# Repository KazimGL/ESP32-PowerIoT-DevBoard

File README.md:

# ESP32 PowerIoT Dev Board

**A battery-powered ESP32 development board with onboard Li-ion charging, protection, regulation, and sensor support — designed end-to-end in KiCad.**

Designed by **Kazim Bhojani** ([KaizBuilts](#)) — a fresher PCB design project built to learn the complete hardware design workflow from schematic to fabrication-ready Gerbers.

---

## 📋 Overview

This board combines four functional subsystems into a single 2-layer PCB:

| Block | Function |
|---|---|
| **Power** | USB-C input, ESD protection, TP4056 Li-ion charging, DW01A + FS8205A battery protection, AP2112K-3.3 regulation, battery voltage sensing |
| **Processor** | ESP32-WROOM-32E module with reset/boot circuitry |
| **Communication** | CH340C USB-UART bridge with auto-program (DTR/RTS reset) circuit, I2C breakout |
| **I/O** | Dual GPIO breakout headers (1×15 each), user LED, user button, BME280 environmental sensor |

---

## ⚙️ Specs

- **MCU:** ESP32-WROOM-32E (WiFi + Bluetooth)
- **Charging:** TP4056, USB-C input, configurable charge current
- **Protection:** DW01A + FS8205A (overcharge / overdischarge / short-circuit)
- **Regulation:** AP2112K-3.3, 600mA LDO
- **Sensor:** BME280 (temperature, humidity, pressure) over I2C
- **Layers:** 2-layer PCB
- **Design tool:** KiCad 10.0.5
- **Board size:** ~65mm × 50mm

---

## 🖼️ Images

**PCB Layout / Routing**

**3D Render**

**Schematic**
📄 [schematic.pdf](schematic.pdf)

**3D Design Overview**
📄 [PRoject_cv.pdf](PRoject_cv.pdf)

---

## 🧠 Design Process & AI-Assisted Workflow

This project was built while learning PCB design fundamentals from scratch, using **Claude (Anthropic)** as a design-review assistant throughout the process — not to generate the design automatically, but to:

- Review each schematic block (Power, Processor, Communication, I/O) for wiring correctness before moving forward
- Explain *why* certain circuits work the way they do (e.g., the EN/IO0 auto-reset logic, battery protection MOSFET gate drive, I2C pull-up sizing)
- Walk through ERC/DRC error messages line-by-line and explain root causes rather than just handing over a fix
- Catch real mistakes along the way (several were my own, and at least one was the AI's — an incorrect DTR/RTS pin mapping that was caught and corrected by cross-checking against esptool's actual reset sequence rather than assumption)

This was an intentionally iterative process: wire a section → verify in ERC → get it reviewed → fix → repeat. Every connection in this board was manually drawn, checked, and understood — the AI's role was review and explanation, not auto-generation.

---

## 🐛 Real Issues Faced During This Build

Documenting these because they were the most time-consuming (and most educational) parts of the project:

1. **KiCad global symbol library table accidentally broken** — while trying to fix a missing footprint library path, the entire global symbol library table collapsed down to a single broken entry, causing 72 cascading ERC warnings across unrelated components (`power`, `Diode`, `Switch`, `Connector` libraries all failed to load). Fixed using KiCad's **"Reset Libraries"** button in the Symbol Libraries manager.

2. **Custom part (FS8205A) had no native KiCad footprint** — imported via `easyeda2kicad` from its LCSC part number, which required linking both a symbol library *and* a separate footprint library (`.pretty` folder) through two different dialogs in two different KiCad editors (Schematic Editor vs. PCB Editor) — not obvious at first.

3. **Duplicate global labels merging unrelated nets** — reused generic labels like `INPUT` and `OUTPUT` in multiple places on the schematic, which KiCad silently merged into a single net across the whole sheet, causing misleading ERC warnings until traced back and renamed to unique, meaningful net names (`VBUS_FUSED`, `3V3`, `-BATT`, etc).

4. **USB-C footprint/symbol pin-count mismatch** — J1 was assigned a 6-pin "power only" USB-C footprint while the schematic symbol used the full 16-pin USB 2.0 pinout (including D+/D−), causing 10 pad-not-found errors during PCB sync. Fixed by selecting the correct 16-pin footprint (`USB_C_Receptacle_HRO_TYPE-C-31-M-12`) matching the real connector's datasheet.

5. **Invalid reference designators blocking PCB sync** — two LED symbols were accidentally named `Green(Done)1` and `RED(charging)1` instead of standard alphanumeric designators, which KiCad's schematic/ERC tolerated but the PCB sync step rejected outright. Renamed to proper `D4`/`D5` format.

6. **DRC hole-size violation on the ESP32 module footprint** — the ESP32-WROOM-32E footprint's castellated pads required a 0.2mm minimum drill size, but the board's design rules were set to a 0.3mm minimum, causing 21 repeated violations. Resolved by adjusting the board's minimum drill size constraint to match both the footprint and the target fab's actual capability.

7. **Incomplete thermal relief connections** on copper pour zones for small shield/ground pads — fixed by reducing the thermal relief gap and spoke width settings to better fit smaller pad geometries.

Each of these was worked through methodically: understand the error → identify root cause → fix → re-verify, rather than blindly applying fixes.

---

## 📁 Repository Contents

```
project_CV.kicad_pro    → KiCad project file
project_CV.kicad_sch    → Schematic source
project_CV.kicad_pcb    → PCB layout source
schematic.pdf           → Exported schematic (all 4 blocks)
PRoject_cv.pdf          → Full project document
*.png                   → PCB layout / 3D render screenshots
README.md               → This file
```

---

## 🔧 Tools Used

- **KiCad 10.0.5** — schematic capture, PCB layout, DRC/ERC
- **easyeda2kicad** — custom part import (FS8205A battery protection MOSFET)
- **Claude (Anthropic)** — design review and debugging assistant

---

---

*Built as a learning project to understand the full PCB design lifecycle — schematic capture, component selection, DFM, fabrication file generation, and bring-up — end to end.*

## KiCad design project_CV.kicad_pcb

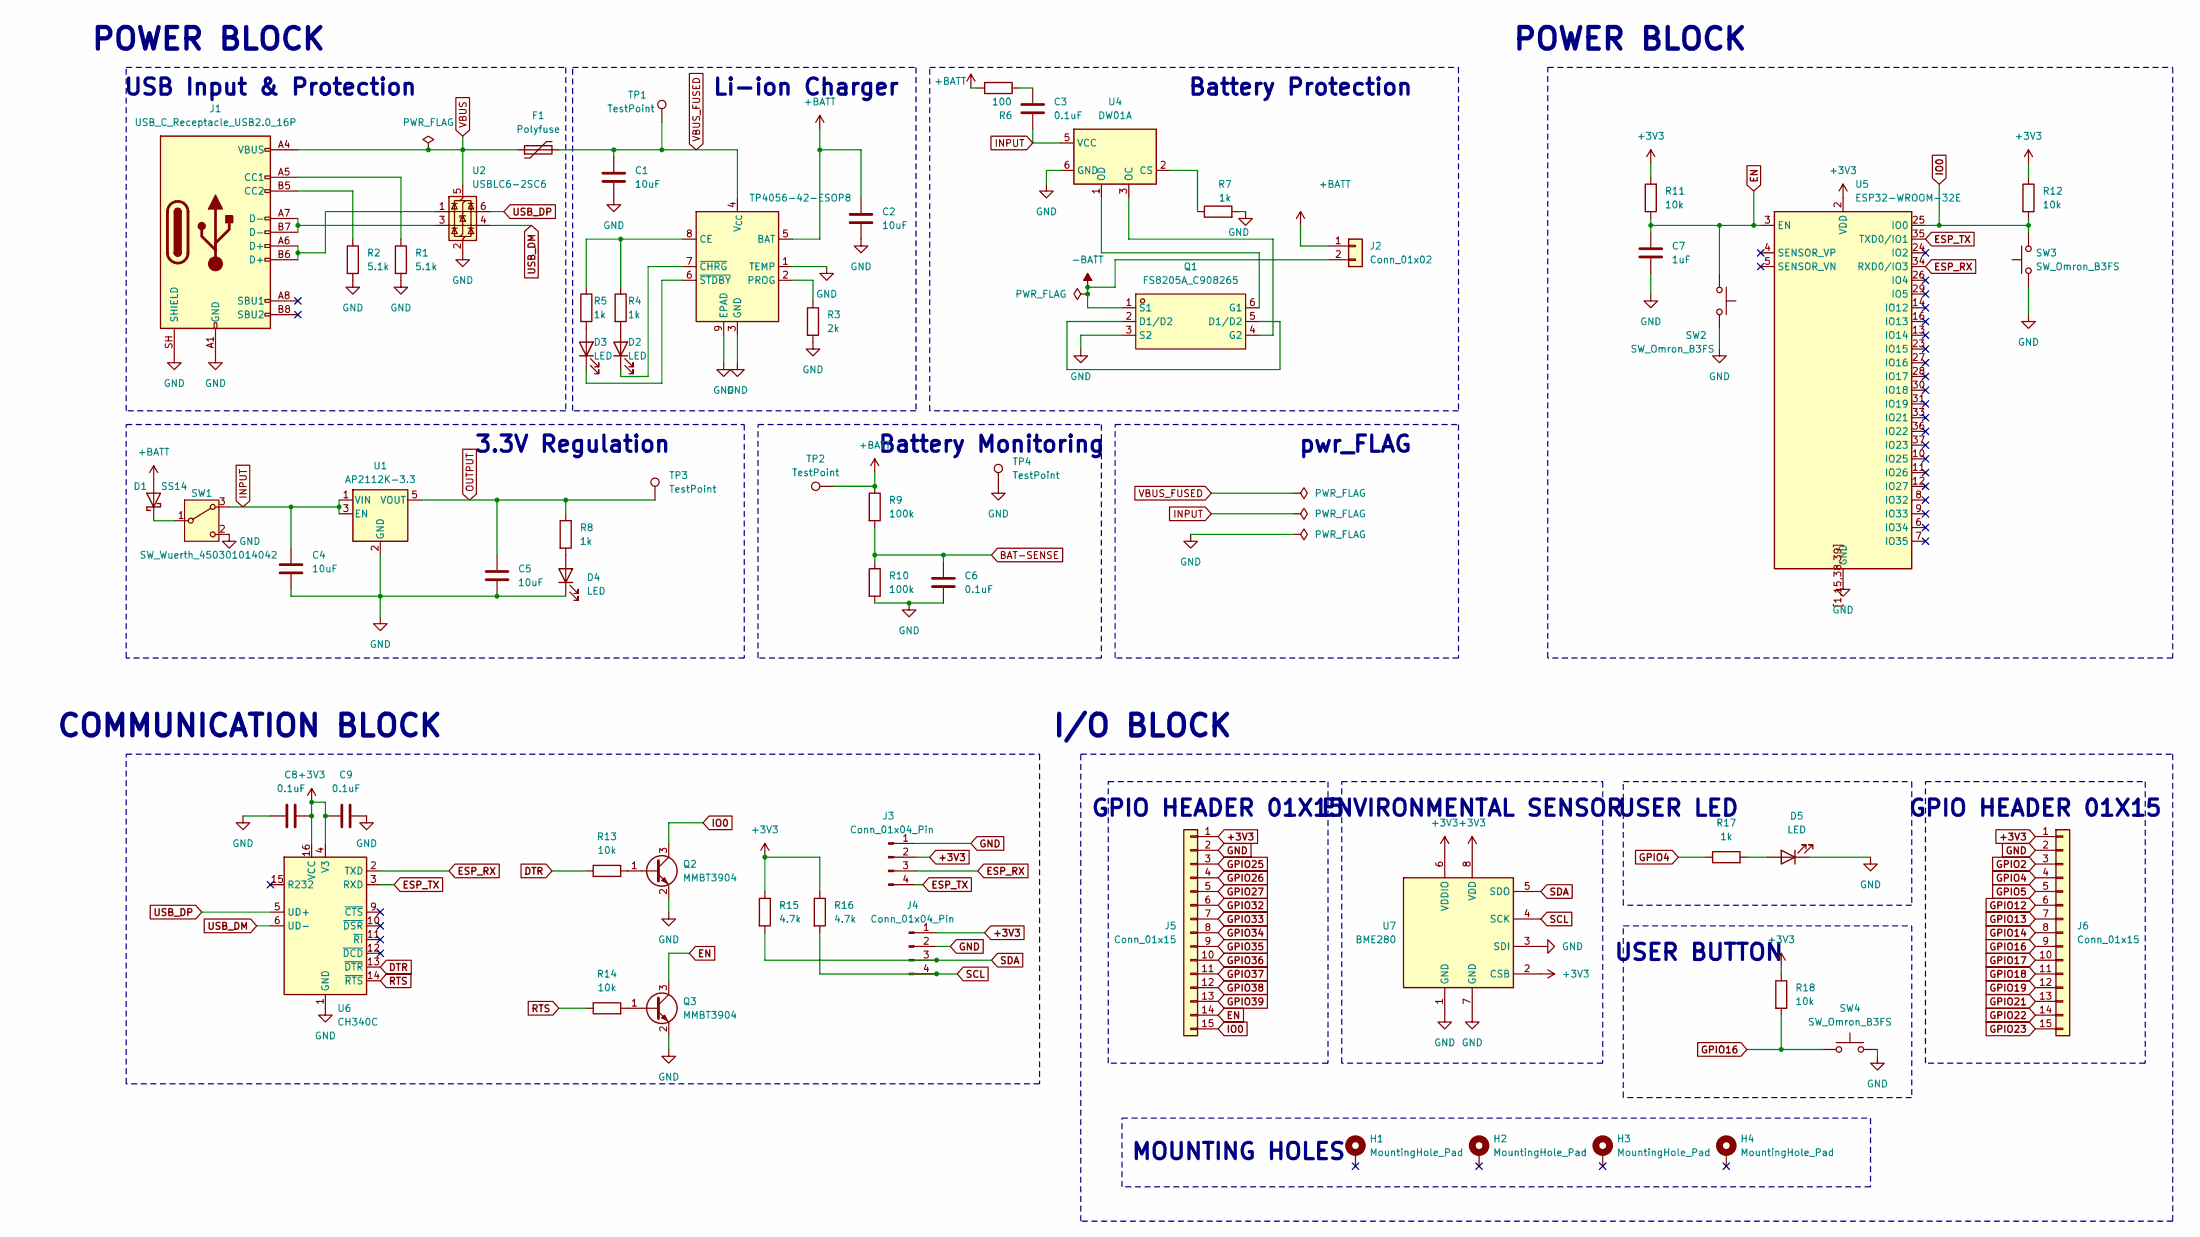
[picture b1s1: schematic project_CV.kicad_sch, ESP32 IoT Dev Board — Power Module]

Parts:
C1, C2, C4, C5: 10uF; C_0805_2012Metric
C3, C6, C8, C9: 0.1uF; C_0603_1608Metric
C7: 1uF; C_0603_1608Metric
D1: SS14; D_SMA
D2, D3, D4, D5: LED; LED_0805_2012Metric
F1: Polyfuse; Fuse_1206_3216Metric
H1, H2, H3, H4: MountingHole_Pad; MountingHole_2.2mm_M2_Pad
J1: USB_C_Receptacle_USB2.0_16P; USB_C_Receptacle_HRO_TYPE-C-31-M-12
J2: Conn_01x02; JST_PH_B2B-PH-K_1x02_P2.00mm_Vertical
J3, J4: Conn_01x04_Pin; PinHeader_1x04_P2.54mm_Vertical
J5, J6: Conn_01x15; PinHeader_1x15_P2.54mm_Vertical
Q1: FS8205A_C908265; SOT-23-6_L2.9-W1.6-P0.95-LS2.8-BR; MPN FS8205A; LCSC Part C908265
Q2, Q3: MMBT3904; SOT-23
R1, R2: 5.1k; R_0603_1608Metric
R3: 2k; R_0603_1608Metric
R4, R5, R7, R8, R17: 1k; R_0603_1608Metric
R6: 100; R_0603_1608Metric
R9, R10: 100k; R_0603_1608Metric
R11, R12, R13, R14, R18: 10k; R_0603_1608Metric
R15, R16: 4.7k; R_0603_1608Metric
SW1: SW_Wuerth_450301014042; SW_SPDT_CK_JS102011SAQN
SW2, SW3, SW4: SW_Omron_B3FS; SW_SPST_TL3342
TP1, TP2, TP3, TP4: TestPoint; TestPoint_Pad_D2.0mm
U1: AP2112K-3.3; SOT-23-5
U2: USBLC6-2SC6; SOT-23-6
U3: TP4056-42-ESOP8; SOIC-8-1EP_3.9x4.9mm_P1.27mm_EP2.41x3.3mm_ThermalVias
U4: DW01A; SOT-23-6
U5: ESP32-WROOM-32E
U6: CH340C; SOIC-16_3.9x9.9mm_P1.27mm
U7: BME280; Bosch_LGA-8_2.5x2.5mm_P0.65mm_ClockwisePinNumbering

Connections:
+3V3: C8.2, C9.1, J3.2, J4.1, J5.1, J6.1, R11.2, R12.1, R15.1, R16.1, R18.1, U5.2 (VDD), U6.4 (V3), U6.16 (VCC), U7.2 (CSB), U7.6 (VDDIO), U7.8 (VDD)
+BATT: C2.1, D1.2 (A), J2.1, R6.2, R9.1, TP2.1 (1_1), U3.5 (BAT)
-BATT: J2.2, Q1.1 (S1)
BAT-SENSE: C6.1, R9.2, R10.1
DTR: R13.1, U6.13 (~DTR)
EN: C7.1, J5.14, Q3.3 (C), R11.1, SW2.1, U5.3 (EN)
ESP_RX: J3.3, U5.34 (RXD0/IO3), U6.2 (TXD)
ESP_TX: J3.4, U5.35 (TXD0/IO1), U6.3 (RXD)
GND: C1.2, C2.2, C4.2, C5.2, C6.2, C7.2, C8.1, C9.2, D4.1 (K), D5.1 (K), J1.A1 (GND), J1.A12 (GND), J1.B1 (GND), J1.B12 (GND), J1.SH (SHIELD), J3.1, J4.2, J5.2, J6.2, Q1.3 (S2), Q2.2 (E), Q3.2 (E), R1.2, R2.2, R3.2, R7.2, R10.2, SW1.2 (C), SW2.2, SW3.1, SW4.2, TP4.1 (1_1), U1.2 (GND), U2.2 (GND), U3.1 (TEMP), U3.3 (GND), U3.9 (EPAD), U4.6 (GND), U5.1 (GND), U5.15 (GND), U5.38 (GND), U5.39 (GND), U5.[1,15,38,39] (GND), U6.1 (GND), U7.1 (GND), U7.3 (SDI), U7.7 (GND); also elsewhere on the board
GPIO2: J6.3
GPIO4: J6.4, R17.1
GPIO5: J6.5
GPIO12: J6.6
GPIO13: J6.7
GPIO14: J6.8
GPIO16: J6.9, R18.2, SW4.1
GPIO17: J6.10
GPIO18: J6.11
GPIO19: J6.12
GPIO21: J6.13
GPIO22: J6.14
GPIO23: J6.15
GPIO25: J5.3
GPIO26: J5.4
GPIO27: J5.5
GPIO32: J5.6
GPIO33: J5.7
GPIO34: J5.8
GPIO35: J5.9
GPIO36: J5.10
GPIO37: J5.11
GPIO38: J5.12
GPIO39: J5.13
INPUT: C3.2, C4.1, SW1.3 (A), U1.1 (VIN), U1.3 (EN), U4.5 (VCC)
IO0: J5.15, Q2.3 (C), R12.2, SW3.2, U5.25 (IO0)
unnamed: C3.1, R6.1
unnamed: D1.1 (K), SW1.1 (B)
unnamed: D2.2 (A), R4.2
unnamed: D2.1 (K), U3.7 (~CHRG)
unnamed: D3.2 (A), R5.2
unnamed: D3.1 (K), U3.6 (~STDBY)
unnamed: D4.2 (A), R8.2
unnamed: D5.2 (A), R17.2
unnamed: J1.A5 (CC1), R1.1
unnamed: J1.B5 (CC2), R2.1
unnamed 45: J1.A6 (D+), J1.B6 (D+), U2.1 (I/O1); also elsewhere on the board
unnamed 46: J1.A7 (D-), J1.B7 (D-), U2.3 (I/O2); also elsewhere on the board
unnamed: Q1.2 (D1/D2), Q1.5 (D1/D2)
unnamed: Q1.6 (G1), U4.1 (OD)
unnamed: Q1.4 (G2), U4.3 (OC)
unnamed: Q2.1 (B), R13.2
unnamed: Q3.1 (B), R14.2
unnamed: R4.1, R5.1, U3.8 (CE)
unnamed: R3.1, U3.2 (PROG)
unnamed: R7.1, U4.2 (CS)
OUTPUT: C5.1, R8.1, TP3.1 (1_1), U1.5 (VOUT)
RTS: R14.1, U6.14 (~RTS)
SCL: J4.4, R16.2, U7.4 (SCK)
SDA: J4.3, R15.2, U7.5 (SDO)
USB_DM: U2.4 (I/O2), U6.6 (UD-); also elsewhere on the board
USB_DP: U2.6 (I/O1), U6.5 (UD+); also elsewhere on the board
VBUS: F1.1, J1.A4 (VBUS), J1.A9 (VBUS), J1.B4 (VBUS), J1.B9 (VBUS), U2.5 (VBUS); also elsewhere on the board
VBUS_FUSED: C1.1, F1.2, TP1.1 (1_1), U3.4 (V_{CC})

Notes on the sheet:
3.3V Regulation
COMMUNICATION BLOCK
USER BUTTON
GPIO HEADER 01X15
I/O BLOCK
Battery Monitoring
USER LED
POWER BLOCK
Li-ion Charger
ENVIRONMENTAL SENSOR
USB Input & Protection
pwr_FLAG
MOUNTING HOLES
Battery Protection

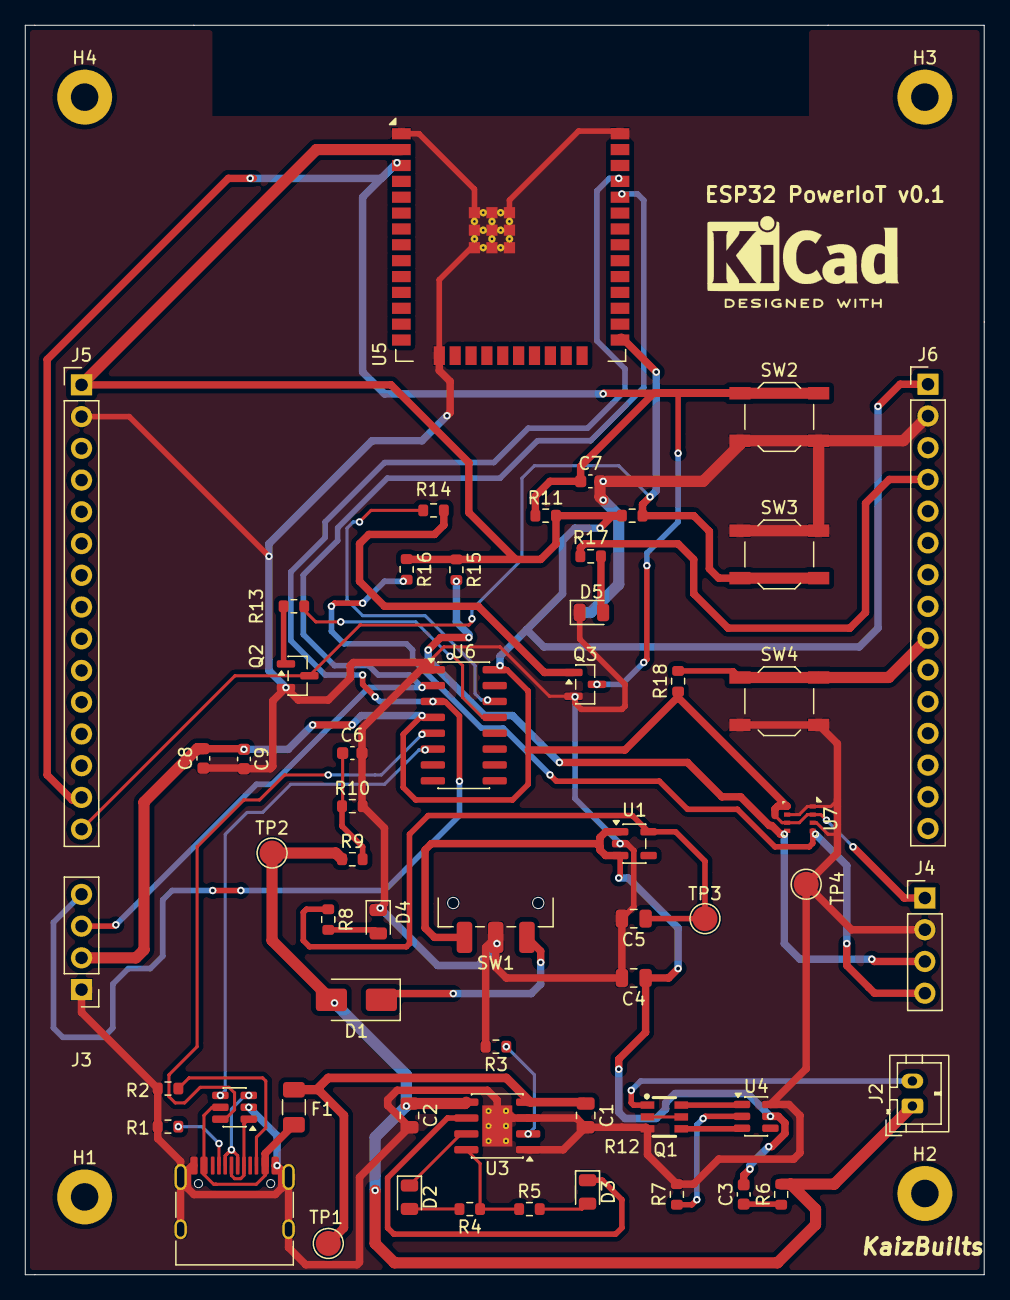
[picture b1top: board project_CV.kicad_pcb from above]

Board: 2 copper layers, 76.8 x 100.0 mm, 61 parts (0 on the bottom side), 41 nets.

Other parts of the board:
Ue: USBLC6-2SC6; SOT-23-6

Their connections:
GND: Ue.2 (GND); also elsewhere on the board
unnamed 45: Ue.1 (I/O1); also elsewhere on the board
unnamed 46: Ue.3 (I/O2); also elsewhere on the board
USB_DM: Ue.4 (I/O2); also elsewhere on the board
USB_DP: Ue.6 (I/O1); also elsewhere on the board
VBUS: Ue.5 (VBUS); also elsewhere on the board

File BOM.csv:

"Reference","Qty","Value","DNP","Exclude from BOM","Exclude from Board","Exclude from Simulation","Exclude from Position Files","Footprint","Datasheet"
"C1,C2,C4,C5","4","10uF","","","","","${EXCLUDE_FROM_POS_FILES}","Capacitor_SMD:C_0805_2012Metric",""
"C3,C6,C8,C9","4","0.1uF","","","","","${EXCLUDE_FROM_POS_FILES}","Capacitor_SMD:C_0603_1608Metric",""
"C7","1","1uF","","","","","${EXCLUDE_FROM_POS_FILES}","Capacitor_SMD:C_0603_1608Metric",""
"D1","1","SS14","","","","","${EXCLUDE_FROM_POS_FILES}","Diode_SMD:D_SMA","https://www.vishay.com/docs/88746/ss12.pdf"
"D2,D3,D4,D5","4","LED","","","","","${EXCLUDE_FROM_POS_FILES}","LED_SMD:LED_0805_2012Metric",""
"F1","1","Polyfuse","","","","","${EXCLUDE_FROM_POS_FILES}","Fuse:Fuse_1206_3216Metric",""
"J1","1","USB_C_Receptacle_USB2.0_16P","","","","","${EXCLUDE_FROM_POS_FILES}","Connector_USB:USB_C_Receptacle_HRO_TYPE-C-31-M-12","https://www.usb.org/sites/default/files/documents/usb_type-c.zip"
"J2","1","Conn_01x02","","","","","${EXCLUDE_FROM_POS_FILES}","Connector_JST:JST_PH_B2B-PH-K_1x02_P2.00mm_Vertical",""
"J3,J4","2","Conn_01x04_Pin","","","","","${EXCLUDE_FROM_POS_FILES}","Connector_PinHeader_2.54mm:PinHeader_1x04_P2.54mm_Vertical",""
"J5,J6","2","Conn_01x15","","","","","${EXCLUDE_FROM_POS_FILES}","Connector_PinHeader_2.54mm:PinHeader_1x15_P2.54mm_Vertical",""
"Q1","1","FS8205A_C908265","","","","","${EXCLUDE_FROM_POS_FILES}","FS8205A_lib:SOT-23-6_L2.9-W1.6-P0.95-LS2.8-BR","https://lcsc.com/product-detail/MOSFET_FUXINSEMI-FS8205A_C90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"
"Q2,Q3","2","MMBT3904","","","","","${EXCLUDE_FROM_POS_FILES}","Package_TO_SOT_SMD:SOT-23","https://www.onsemi.com/pdf/datasheet/pzt3904-d.pdf"
"R1,R2","2","5.1k","","","","","${EXCLUDE_FROM_POS_FILES}","Resistor_SMD:R_0603_1608Metric",""
"R3","1","2k","","","","","${EXCLUDE_FROM_POS_FILES}","Resistor_SMD:R_0603_1608Metric",""
"R4,R5,R7,R8,R17","5","1k","","","","","${EXCLUDE_FROM_POS_FILES}","Resistor_SMD:R_0603_1608Metric",""
"R6","1","100","","","","","${EXCLUDE_FROM_POS_FILES}","Resistor_SMD:R_0603_1608Metric",""
"R9,R10","2","100k","","","","","${EXCLUDE_FROM_POS_FILES}","Resistor_SMD:R_0603_1608Metric",""
"R11,R12,R13,R14,R18","5","10k","","","","","${EXCLUDE_FROM_POS_FILES}","Resistor_SMD:R_0603_1608Metric",""
"R15,R16","2","4.7k","","","","","${EXCLUDE_FROM_POS_FILES}","Resistor_SMD:R_0603_1608Metric",""
"SW1","1","SW_Wuerth_450301014042","","","","","${EXCLUDE_FROM_POS_FILES}","Button_Switch_SMD:SW_SPDT_CK_JS102011SAQN","https://www.we-online.com/components/products/datasheet/4503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"
"SW2,SW3,SW4","3","SW_Omron_B3FS","","","","","${EXCLUDE_FROM_POS_FILES}","Button_Switch_SMD:SW_SPST_TL3342","https://omronfs.omron.com/en_US/ecb/products/pdf/en-b3fs.pdf"
"TP1,TP2,TP3,TP4","4","TestPoint","","","","","${EXCLUDE_FROM_POS_FILES}","TestPoint:TestPoint_Pad_D2.0mm",""
"U1","1","AP2112K-3.3","","","","","${EXCLUDE_FROM_POS_FILES}","Package_TO_SOT_SMD:SOT-23-5","https://www.diodes.com/assets/Datasheets/AP2112.pdf"
"U2","1","USBLC6-2SC6","","","","","${EXCLUDE_FROM_POS_FILES}","Package_TO_SOT_SMD:SOT-23-6","https://www.st.com/resource/en/datasheet/usblc6-2.pdf"
"U3","1","TP4056-42-ESOP8","","","","","${EXCLUDE_FROM_POS_FILES}","Package_SO:SOIC-8-1EP_3.9x4.9mm_P1.27mm_EP2.41x3.3mm_ThermalVias","https://www.lcsc.com/datasheet/lcsc_datasheet_2410121619_TOP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"
"U4","1","DW01A","","","","","${EXCLUDE_FROM_POS_FILES}","Package_TO_SOT_SMD:SOT-23-6","https://hmsemi.com/downfile/DW01A.PDF"
"U5","1","ESP32-WROOM-32E","","","","","${EXCLUDE_FROM_POS_FILES}","RF_Module:ESP32-WROOM-32E","https://www.espressif.com/sites/default/files/documentation/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"
"U6","1","CH340C","","","","","${EXCLUDE_FROM_POS_FILES}","Package_SO:SOIC-16_3.9x9.9mm_P1.27mm","https://datasheet.lcsc.com/szlcsc/Jiangsu-Qin-Heng-CH340C_C8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"
"U7","1","BME280","","","","","${EXCLUDE_FROM_POS_FILES}","Package_LGA:Bosch_LGA-8_2.5x2.5mm_P0.65mm_ClockwisePinNumbering","https://www.bosch-sensortec.com/media/boschsensortec/downloa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"
